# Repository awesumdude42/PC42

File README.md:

# Parent Communicator 42

Also known as the PC42, this device allows my parents my parents to call me downstairs for whatever purpose they need. My desk is upstairs in my room and my dining table/kitchen/ living room are all below my room. whenever my parents need me for a meal or if they just want to spend time with me, they need to yell from their floor up to my room. This impacts their voice and often times, the need to call me multiple times because sometimes I don't hear them or I need a few minutes. My device lets them click a button downstairs that triggers a loud and obnoxious alarm that keeps ringing until I go downstairs and turn the alarm off on the parent module. My parents can also opt to use a PA system in order to communicate a message to me like "Go take the dog on a walk" or something similar so I know what I am being called for! There are two modules to this. The Parent module(P module) that is downstairs and is for my parents and the Child module(C module) which is for me and is in my room. The P and C modules have their own unique features:

## P Module features
* PA system
* Alarm Button
* Child turn off button
* LED do not disturb indicator

## C Module fatures
* Speaker
* Do not disturb toggle
* Snooze button(stops working after snoozing a certain amount of times so I actually go down)

## PCB

The PCB is completely modular and only the neccessary parts can be plugged in for each module. This minimizes PCB cost :). The PCB is also hooked up to a 1200mAh LiPo battery and is USBC chargable.

## P Module Case

## C Module Case

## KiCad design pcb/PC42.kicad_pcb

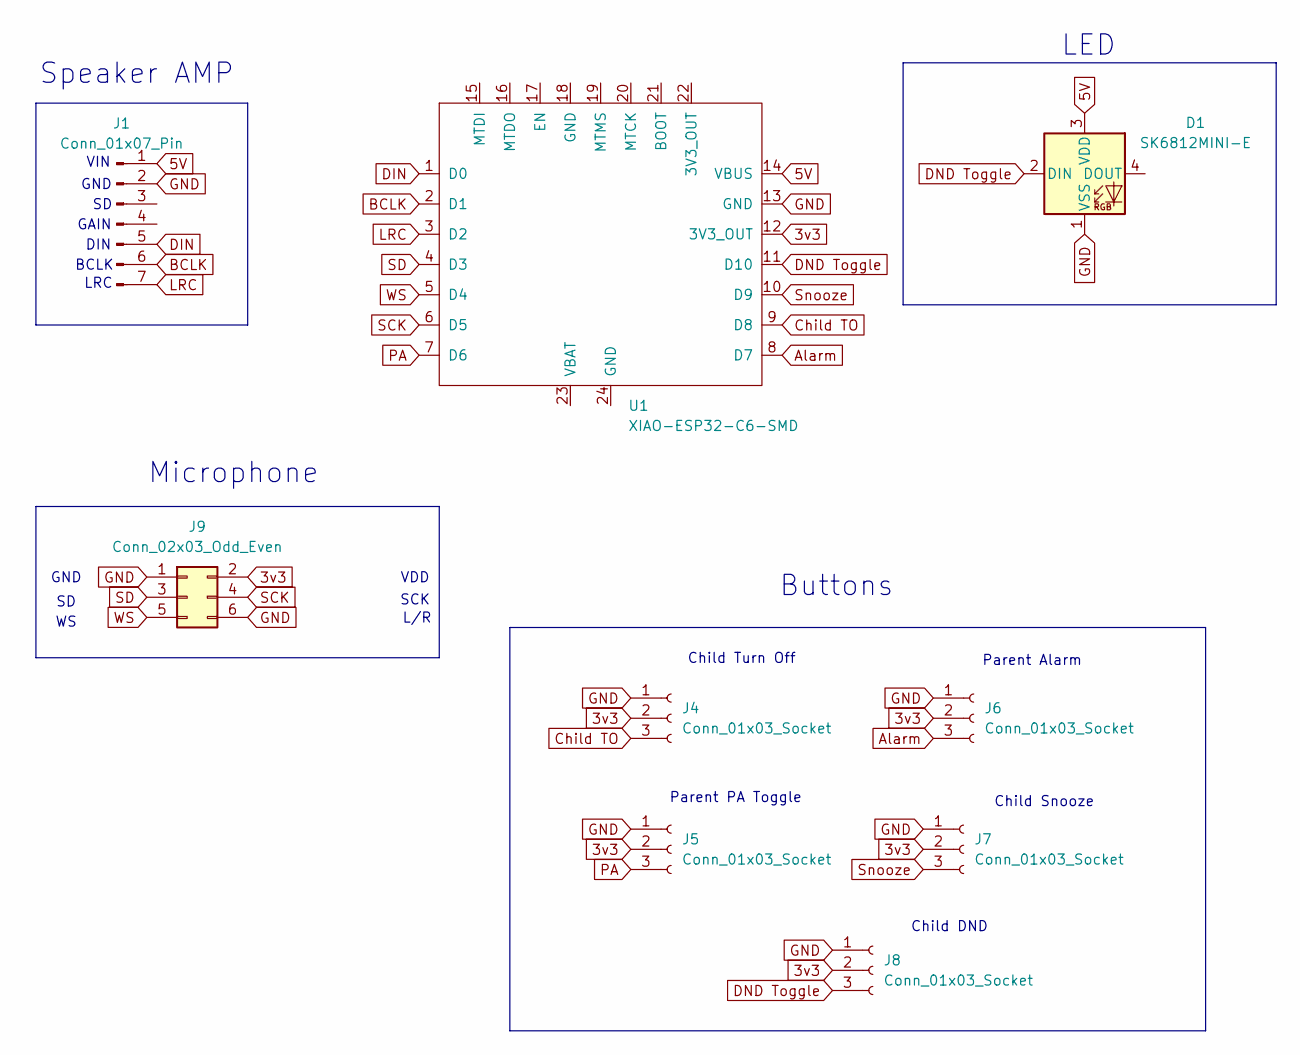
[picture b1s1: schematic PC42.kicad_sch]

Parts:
D1: SK6812MINI-E; LED_SK6812MINI-E_3.2x2.8mm_P1.5mm_ReverseMount
J1: Conn_01x07_Pin; PinHeader_1x07_P2.54mm_Vertical
J4, J5, J6, J7, J8: Conn_01x03_Socket; PinSocket_1x03_P2.54mm_Vertical
J9: Conn_02x03_Odd_Even; INMP441_OMNIDIRECTIONAL_MICROPHONE_MODULE
U1: XIAO-ESP32-C6-SMD; XIAO-ESP32-C6-DIP

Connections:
3v3: J4.2, J5.2, J6.2, J7.2, J8.2, J9.2, U1.12 (3V3_OUT)
5V: D1.3 (VDD), J1.1, U1.14 (VBUS)
Alarm: J6.3, U1.8 (D7)
BCLK: J1.6, U1.2 (D1)
Child TO: J4.3, U1.9 (D8)
DIN: J1.5, U1.1 (D0)
DND Toggle: D1.2 (DIN), J8.3, U1.11 (D10)
GND: D1.1 (VSS), J1.2, J4.1, J5.1, J6.1, J7.1, J8.1, J9.1, J9.6, U1.13 (GND)
LRC: J1.7, U1.3 (D2)
PA: J5.3, U1.7 (D6)
SCK: J9.4, U1.6 (D5)
SD: J9.3, U1.4 (D3)
Snooze: J7.3, U1.10 (D9)
WS: J9.5, U1.5 (D4)

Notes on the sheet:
Parent Alarm
LED
BCLK
VIN
GAIN
Child Snooze
GND
Child Turn Off
Microphone
LRC
VDD
DIN
GND
Speaker AMP
L/R
Parent PA Toggle
Buttons
SCK
Child DND

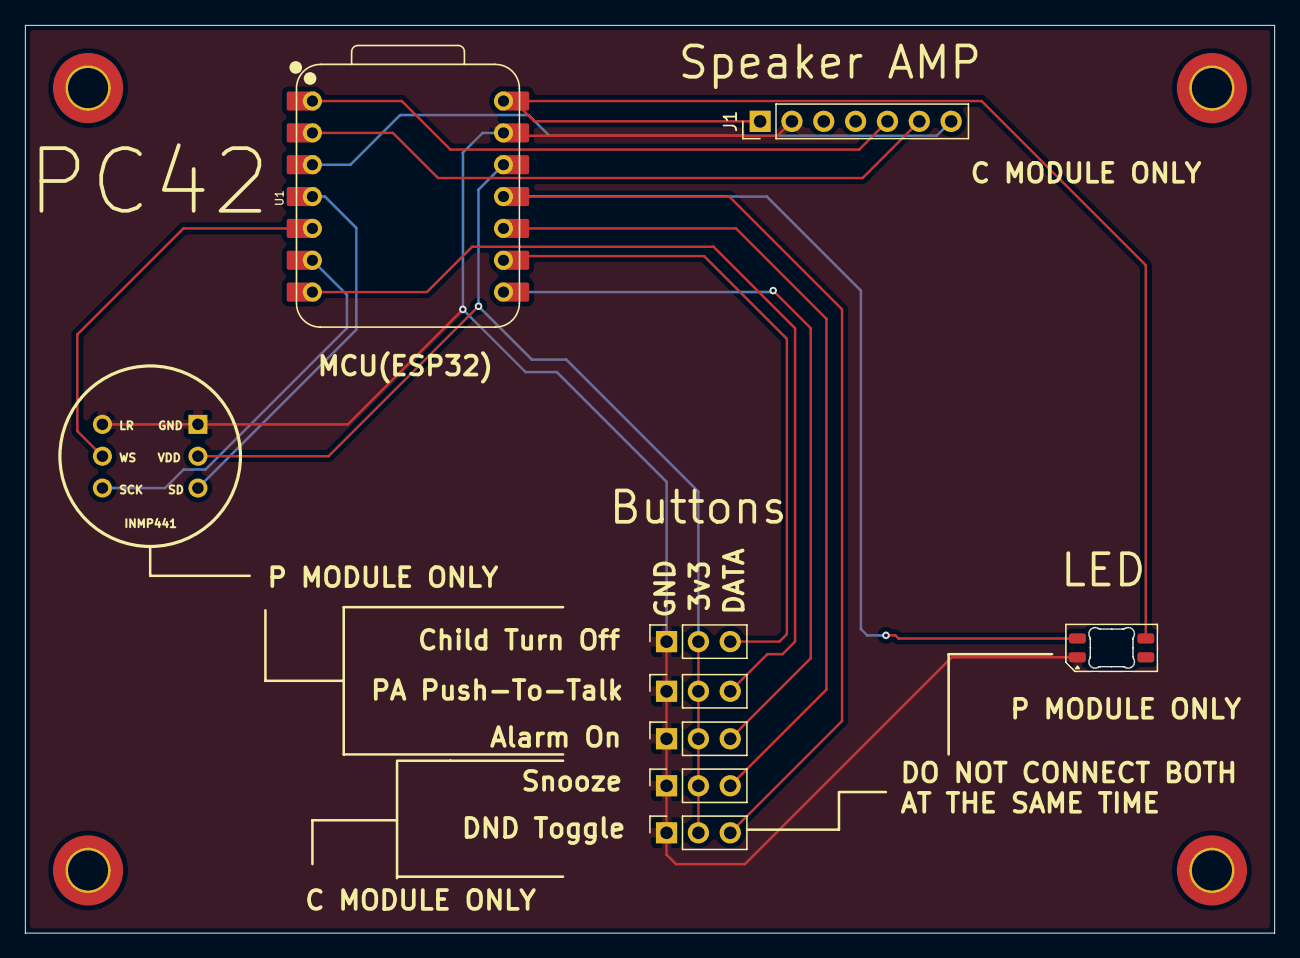
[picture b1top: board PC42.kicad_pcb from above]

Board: 2 copper layers, 99.6 x 72.4 mm, 9 parts (0 on the bottom side), 14 nets.
